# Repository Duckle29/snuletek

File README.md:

# Snuletek.org

This is my old (first) website. I wanted to cancle my plan with my old host, but I couldn't kill my first site, so I wanted to move it to my main server. For that I now store it here.

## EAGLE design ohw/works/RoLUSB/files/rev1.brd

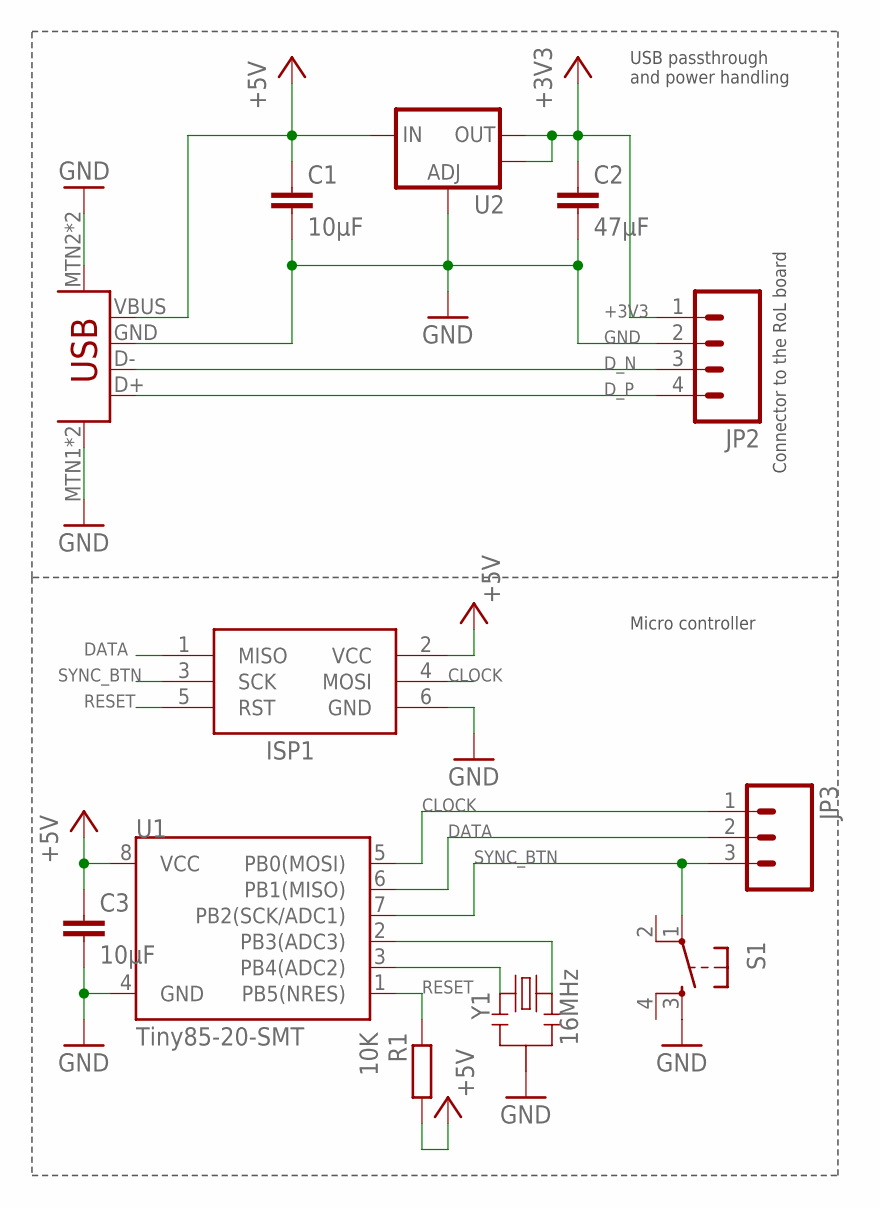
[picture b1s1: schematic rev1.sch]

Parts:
C1, C3: 10µF; C3216
C2: 47µF; C3216
ISP1: AVRISP-6; AVRISP
JP1: USBSMD; USB-MINIB
JP2: M04LOCK; 1X04_LOCK
JP3: M03LOCK; 1X03_LOCK
R1: 10K; R0603
S1: TAC_SWITCHPTH; TACTILE-PTH
U1: Tiny85-20-SMT; SO08-EIAJ
U2: V_REG_LM1117SOT223; SOT223
Y1: 16MHz; RESONATOR-SMD

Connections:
+3V3: C2.1, JP2.1, U2.2 (OUT), U2.4 (OUT)
+5V: C1.1, C3.1, ISP1.2 (VCC), JP1.VBUS, R1.2, U1.8 (VCC), U2.3 (IN)
CLOCK: ISP1.4 (MOSI), JP3.1, U1.5 (PB0(MOSI))
DATA: ISP1.1 (MISO), JP3.2, U1.6 (PB1(MISO))
D_N: JP1.D-, JP2.3
D_P: JP1.D+, JP2.4
GND: C1.2, C2.2, C3.2, ISP1.6 (GND), JP1.GND, JP1.MTN1 (MNT), JP1.MTN2 (MNT2), JP1.MTN3 (MNT2), JP1.MTN4 (MNT), JP2.2, S1.3, U1.4 (GND), U2.1 (ADJ), Y1.2
unnamed: U1.2 (PB3(ADC3)), Y1.3
unnamed: U1.3 (PB4(ADC2)), Y1.1
RESET: ISP1.5 (RST), R1.1, U1.1 (PB5(NRES))
SYNC_BTN: ISP1.3 (SCK), JP3.3, S1.1, U1.7 (PB2(SCK/ADC1))

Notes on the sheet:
Connector to the RoL board
USB passthrough and power handling
Micro controller

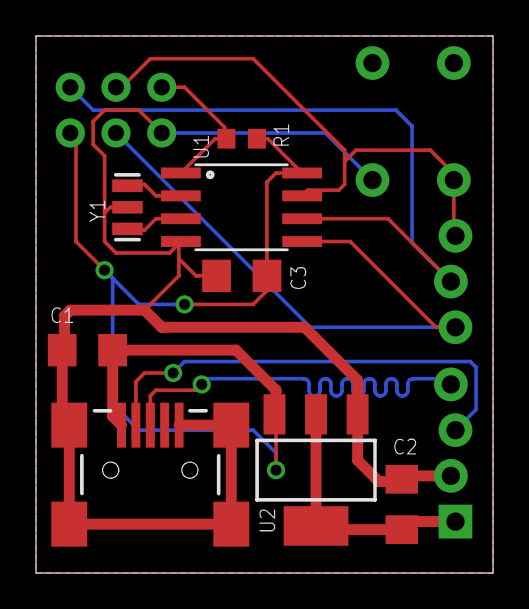
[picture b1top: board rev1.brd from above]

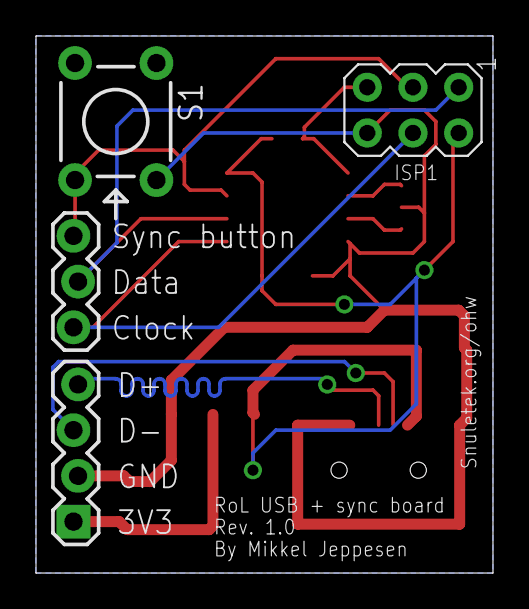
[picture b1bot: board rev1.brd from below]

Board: 2 copper layers, 25.4 x 29.8 mm, 12 parts (4 on the bottom side), 11 nets.

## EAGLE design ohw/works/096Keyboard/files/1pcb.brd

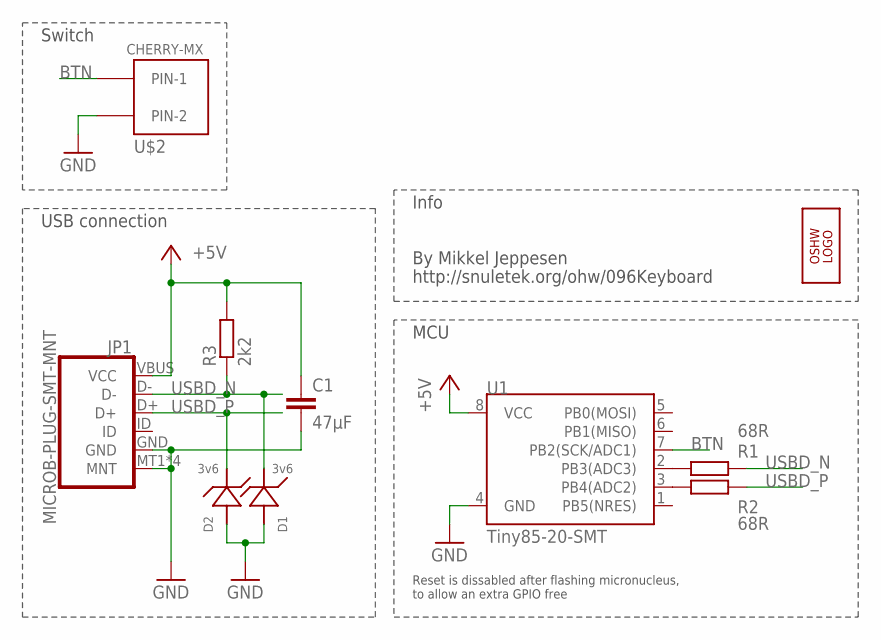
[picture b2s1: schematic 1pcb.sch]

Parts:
C1: 47µF; C3216
D1, D2: 3v6; SOD-523
JP1: MICROB-PLUG-SMT-MNT; USB-MICROB
LOGO1: OSHW_LOGO_6MILX0070-NT; OSHW_6X70_NOTEXT
R1, R2: 68R; R0603
R3: 2k2; R0603
U1: Tiny85-20-SMT; SO08-EIAJ
U$2: CHERRY-MX-I

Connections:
+5V: C1.1, JP1.VBUS (VCC), R3.2, U1.8 (VCC)
BTN: U1.7 (PB2(SCK/ADC1)), U$2.PIN-1
GND: C1.2, D1.A, D2.A, JP1.GND, JP1.MT1 (MNT), JP1.MT2 (MNT), JP1.P$1 (MNT), JP1.P$2 (MNT), U1.4 (GND), U$2.PIN-2
unnamed: R1.1, U1.2 (PB3(ADC3))
unnamed: R2.1, U1.3 (PB4(ADC2))
USBD_N: D1.C, JP1.D-, R1.2, R3.1
USBD_P: D2.C, JP1.D+, R2.2

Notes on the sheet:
http://snuletek.org/ohw/096Keyboard
MCU
Reset is dissabled after flashing micronucleus, to allow an extra GPIO free
USB connection
Switch
Info
By Mikkel Jeppesen

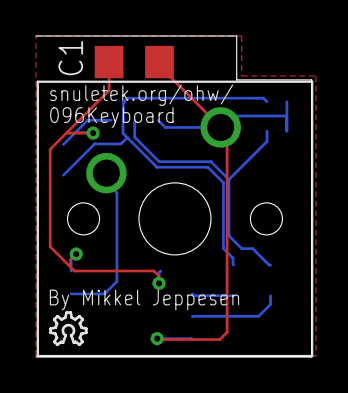
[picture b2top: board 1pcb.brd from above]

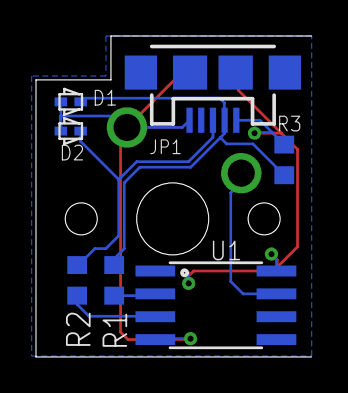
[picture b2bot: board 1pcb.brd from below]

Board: 2 copper layers, 15.3 x 17.8 mm, 10 parts (7 on the bottom side), 7 nets.

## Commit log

2021-09-23 Added RolUSB

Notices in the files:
parts and their libraries:
SparkFun-Connectors: Licensing: CC v3.0 Share-Alike You are welcome to use this library for commercial purposes.
